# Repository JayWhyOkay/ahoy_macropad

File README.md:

# Ahoy -- XT Macropad

Ahoy is a simple but functional macropad designed for people who need both a numpad and a macro column for work/productivity. The features include:

- Numpad with split mod support
- 10 additional keys for macros
- Rotary encoder support on top left key
- 8 addressable RGB LEDs 
- Num, Caps, Scroll Lock Indicator LEDs
- USB C (USB 2.0)

The layout for the macropad can be seen below: 

## Instructions
To replicate the PCB and the case, the guide can be found below: 
- [Instructions on ordering this PCB](ahoy_pcb/gerber/production/)
- [Instructions on ordering the case](acrylic_case/)

## Project Status
- [x] Design PCB
- [x] Design Case
- [x] Order Prototypes
- [x] Create bootloader
- [x] Create QMK/VIA firmware
- [x] Revise prototypes
### Todo List
- [x] Revise LED cutouts on acrylic case 
- [ ] \(Optional) add art/silkscreen
- [ ] Clear @todo 's
- [ ] Update to modern QMK standards!
## Licensing 
The following project was built on Gondolindrim's [Acheron Project](https://github.com/AcheronProject) and ai03's [PCB guide](https://wiki.ai03.com/books/pcb-design/chapter/pcb-designer-guide) and [design files](https://github.com/ai03-2725). As such, the licensing will follow their licensing arrangement on top of this project's licensing, which can be found [here](LICENSE).

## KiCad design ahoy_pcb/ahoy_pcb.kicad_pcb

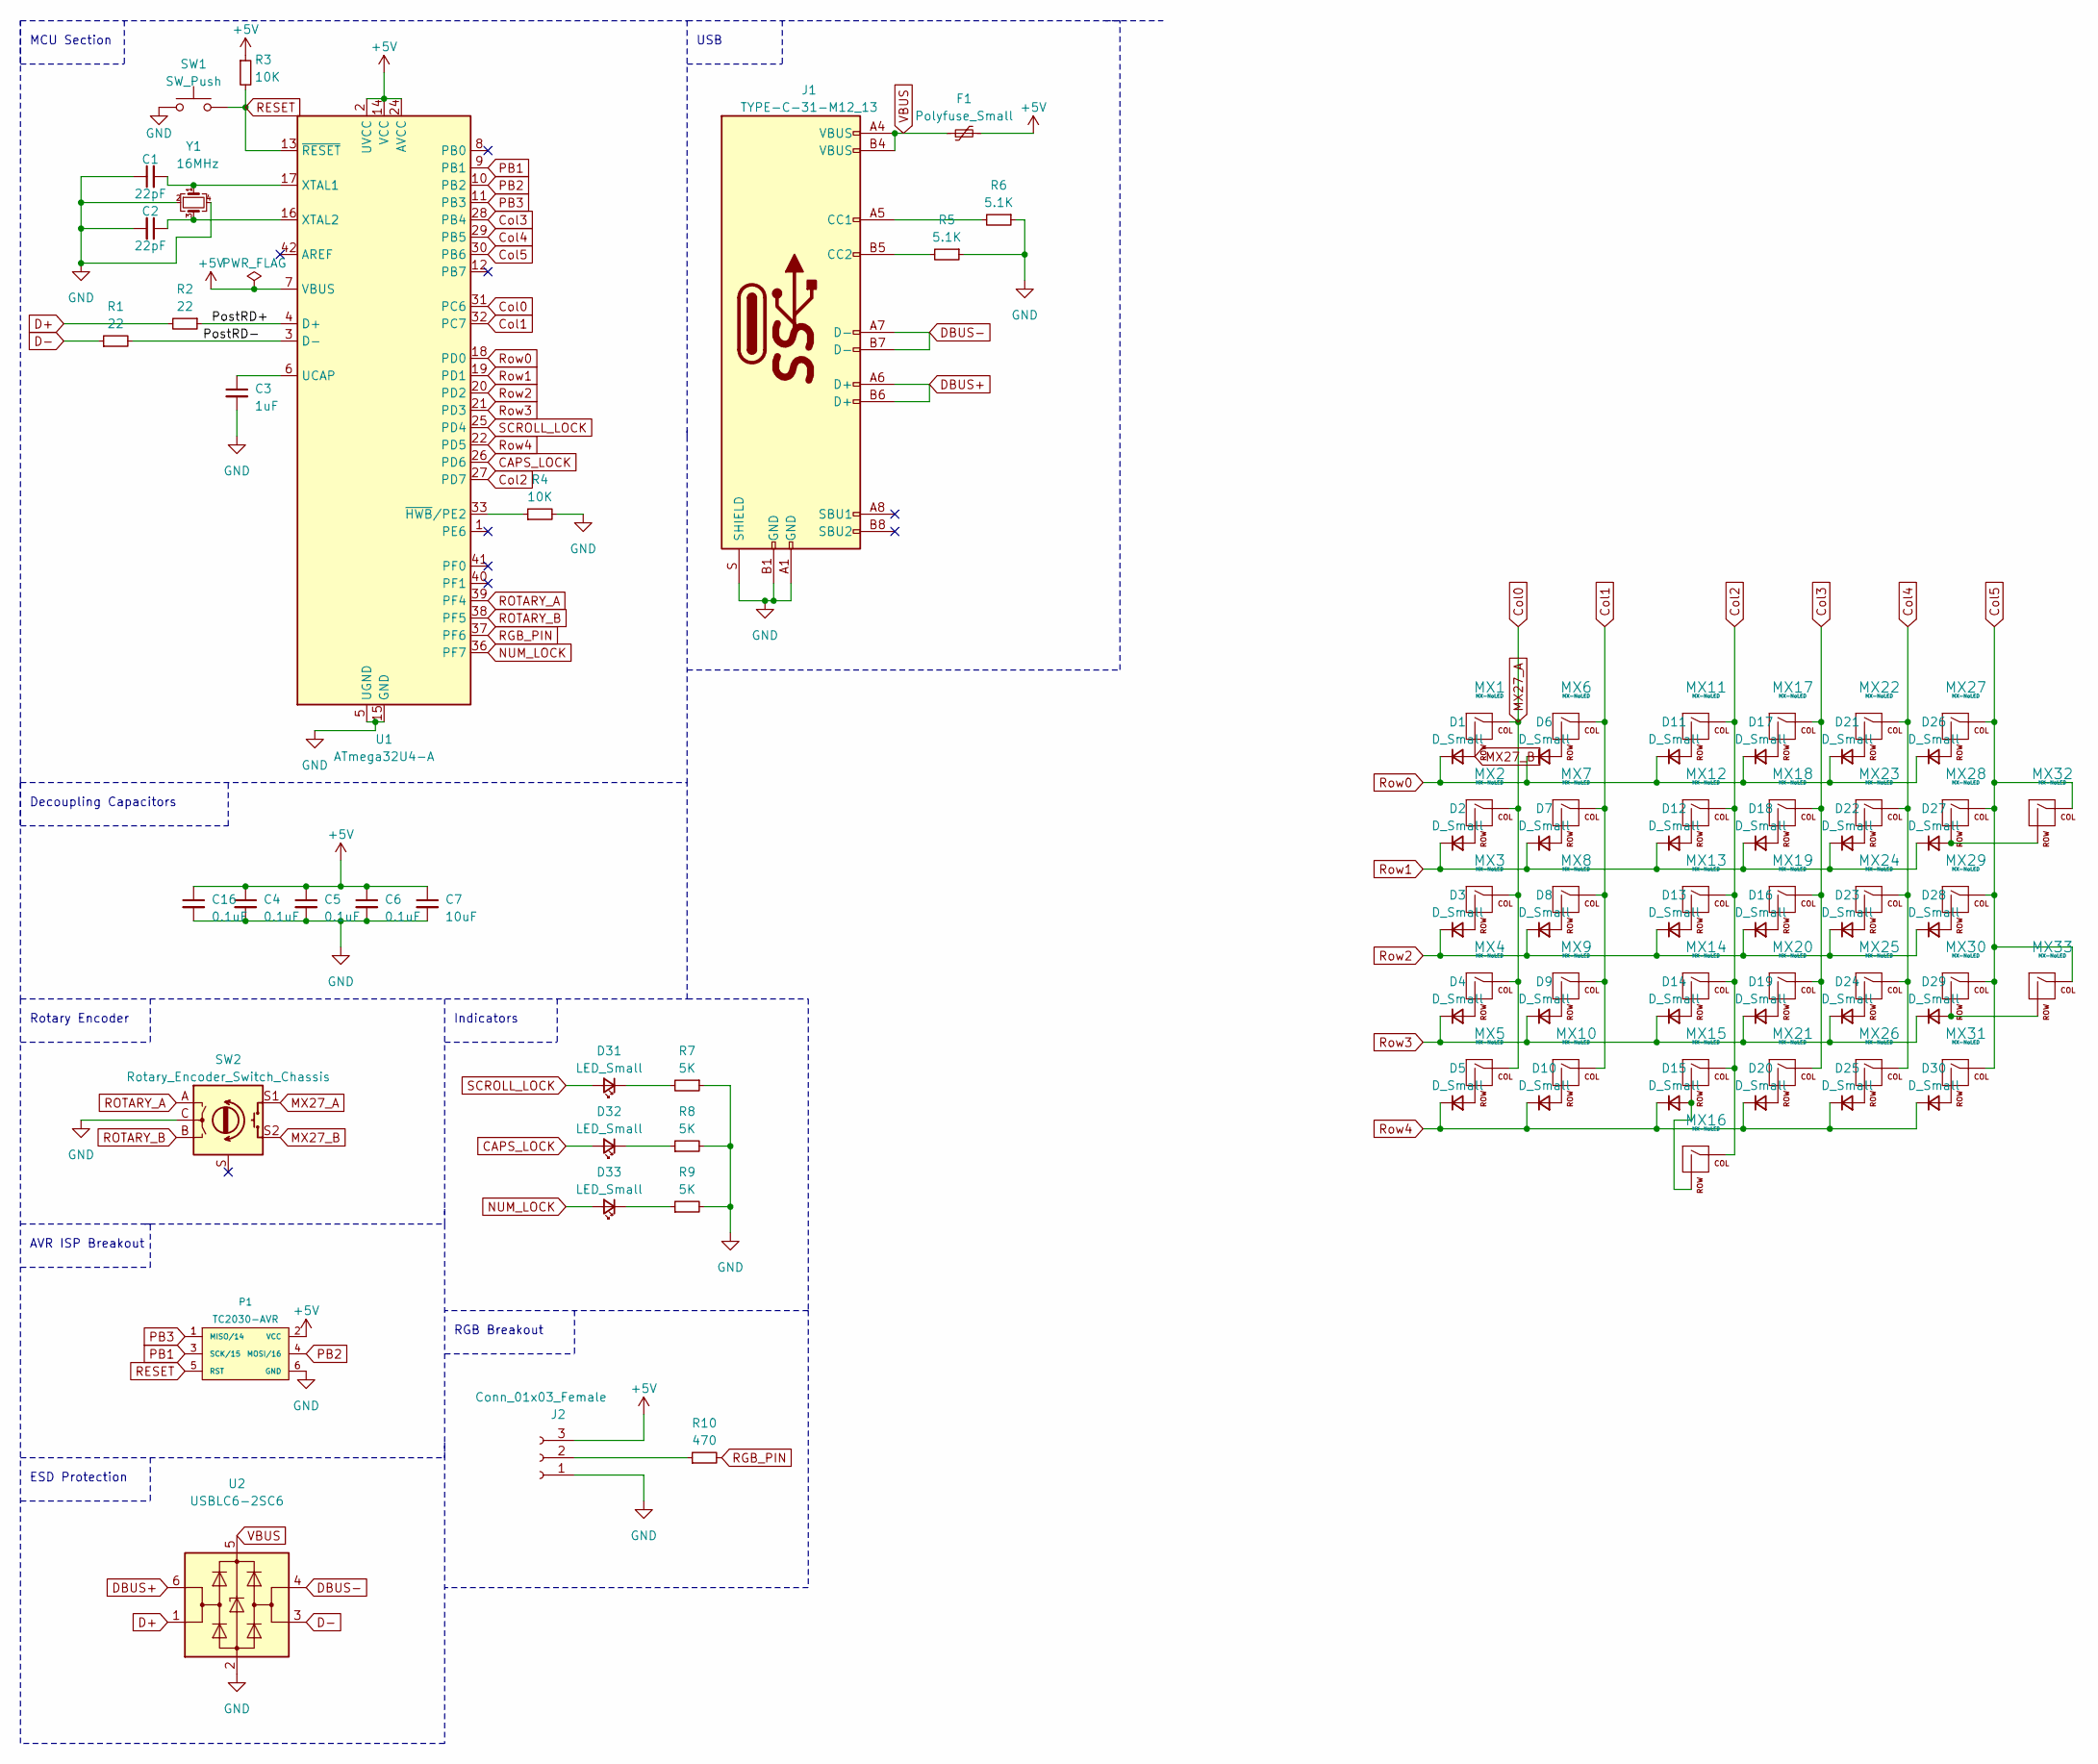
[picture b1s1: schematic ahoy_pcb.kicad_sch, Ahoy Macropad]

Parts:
C1, C2: 22pF; C_0805_2012Metric
C3: 1uF; C_0805_2012Metric
C4, C5, C6, C16: 0.1uF; C_0805_2012Metric
C7: 10uF; C_0805_2012Metric
D1, D2, D3, D4, D5, D6, D7, D8, D9, D10, D11, D12, D13, D14, D15, D16, D17, D18, D19, D20, D21, D22, D23, D24, D25, D26, D27, D28, D29, D30: D_Small; D_SOD-123
D31, D32, D33: LED_Small; LED_D3.0mm-Pretty
F1: Polyfuse_Small; Fuse_1206_3216Metric
J1: TYPE-C-31-M12_13; TYPE-C-31-M-12
J2: Conn_01x03_Female; PinHeader_1x3_staggered_P2.54mm_Vertical
MX1, MX2, MX3, MX4, MX5, MX6, MX7, MX8, MX9, MX10, MX11, MX12, MX13, MX14, MX15, MX17, MX18, MX19, MX20, MX21, MX22, MX23, MX24, MX25, MX26, MX27, MX28, MX29, MX30, MX31: MX-NoLED; MXOnly-1U-NoLED
MX16, MX32, MX33: MX-NoLED; MXOnly-2U-ReversedStabilizers-NoLED
P1: TC2030-AVR; PinHeader_2x3_P2.54mm_Vertical
R1, R2: 22; R_0805_2012Metric
R3, R4: 10K; R_0805_2012Metric
R5, R6: 5.1K; R_0805_2012Metric
R7, R8, R9: 5K; R_0805_2012Metric
R10: 470; R_0805_2012Metric
SW1: SW_Push; SW_TS-1187A-B-A-B
SW2: Rotary_Encoder_Switch_Chassis; RotaryEncoder_Alps_EC11E-Switch_Vertical_H20mm_CircularMoun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
U1: ATmega32U4-A; TQFP-44_10x10mm_P0.8mm
U2: USBLC6-2SC6; SOT-23-6
Y1: 16MHz; Crystal_SMD_3225-4Pin_3.2x2.5mm

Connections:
+5V: C4.1, C5.1, C6.1, C7.1, C16.1, F1.2, J2.3, P1.2 (VCC), R3.1, U1.2 (UVCC), U1.7 (VBUS), U1.14 (VCC), U1.24 (AVCC), U1.34 (VCC), U1.44 (AVCC)
/PostRD+: R2.1, U1.4 (D+)
/PostRD-: R1.2, U1.3 (D-)
CAPS_LOCK: D32.2 (A), U1.26 (PD6)
Col0: MX1.1 (COL), MX2.1 (COL), MX3.1 (COL), MX4.1 (COL), MX5.1 (COL), SW2.S1, U1.31 (PC6)
Col1: MX6.1 (COL), MX7.1 (COL), MX8.1 (COL), MX9.1 (COL), MX10.1 (COL), U1.32 (PC7)
Col2: MX11.1 (COL), MX12.1 (COL), MX13.1 (COL), MX14.1 (COL), MX15.1 (COL), MX16.1 (COL), U1.27 (PD7)
Col3: MX17.1 (COL), MX18.1 (COL), MX19.1 (COL), MX20.1 (COL), MX21.1 (COL), U1.28 (PB4)
Col4: MX22.1 (COL), MX23.1 (COL), MX24.1 (COL), MX25.1 (COL), MX26.1 (COL), U1.29 (PB5)
Col5: MX27.1 (COL), MX28.1 (COL), MX29.1 (COL), MX30.1 (COL), MX31.1 (COL), MX32.1 (COL), MX33.1 (COL), U1.30 (PB6)
D+: R2.2, U2.1 (I/O1)
D-: R1.1, U2.3 (I/O2)
DBUS+: J1.A6 (D+), J1.B6 (D+), U2.6 (I/O1)
DBUS-: J1.A7 (D-), J1.B7 (D-), U2.4 (I/O2)
GND: C1.1, C2.2, C3.2, C4.2, C5.2, C6.2, C7.2, C16.2, J1.A1 (GND), J1.B1 (GND), J1.S (SHIELD), J2.1, P1.6 (GND), R4.2, R5.1, R6.1, R7.1, R8.2, R9.2, SW1.1, SW2.C, U1.5 (UGND), U1.15 (GND), U1.23 (GND), U1.35 (GND), U1.43 (GND), U2.2 (GND), Y1.2, Y1.4
MX27_B: D1.2 (A), MX1.2 (ROW), SW2.S2
NUM_LOCK: D33.2 (A), U1.36 (PF7)
unnamed: C1.2, U1.17 (XTAL1), Y1.1
unnamed: C2.1, U1.16 (XTAL2), Y1.3
unnamed: C3.1, U1.6 (UCAP)
unnamed: D2.2 (A), MX2.2 (ROW)
unnamed: D3.2 (A), MX3.2 (ROW)
unnamed: D4.2 (A), MX4.2 (ROW)
unnamed: D5.2 (A), MX5.2 (ROW)
unnamed: D6.2 (A), MX6.2 (ROW)
unnamed: D7.2 (A), MX7.2 (ROW)
unnamed: D8.2 (A), MX8.2 (ROW)
unnamed: D9.2 (A), MX9.2 (ROW)
unnamed: D10.2 (A), MX10.2 (ROW)
unnamed: D11.2 (A), MX11.2 (ROW)
unnamed: D12.2 (A), MX12.2 (ROW)
unnamed: D13.2 (A), MX13.2 (ROW)
unnamed: D14.2 (A), MX14.2 (ROW)
unnamed: D15.2 (A), MX15.2 (ROW), MX16.2 (ROW)
unnamed: D16.2 (A), MX19.2 (ROW)
unnamed: D17.2 (A), MX17.2 (ROW)
unnamed: D18.2 (A), MX18.2 (ROW)
unnamed: D19.2 (A), MX20.2 (ROW)
unnamed: D20.2 (A), MX21.2 (ROW)
unnamed: D21.2 (A), MX22.2 (ROW)
unnamed: D22.2 (A), MX23.2 (ROW)
unnamed: D23.2 (A), MX24.2 (ROW)
unnamed: D24.2 (A), MX25.2 (ROW)
unnamed: D25.2 (A), MX26.2 (ROW)
unnamed: D26.2 (A), MX27.2 (ROW)
unnamed: D27.2 (A), MX28.2 (ROW), MX32.2 (ROW)
unnamed: D28.2 (A), MX29.2 (ROW)
unnamed: D29.2 (A), MX30.2 (ROW), MX33.2 (ROW)
unnamed: D30.2 (A), MX31.2 (ROW)
unnamed: D31.1 (K), R7.2
unnamed: D32.1 (K), R8.1
unnamed: D33.1 (K), R9.1
unnamed: J1.A5 (CC1), R6.2
unnamed: J1.B5 (CC2), R5.2
unnamed: R4.1, U1.33 (~HWB~/PE2)
unnamed: J2.2, R10.1
PB1: P1.3 (SCK/15), U1.9 (PB1)
PB2: P1.4 (MOSI/16), U1.10 (PB2)
PB3: P1.1 (MISO/14), U1.11 (PB3)
RESET: P1.5 (RST), R3.2, SW1.2, U1.13 (~RESET)
RGB_PIN: R10.2, U1.37 (PF6)
ROTARY_A: SW2.A, U1.39 (PF4)
ROTARY_B: SW2.B, U1.38 (PF5)
Row0: D1.1 (K), D6.1 (K), D11.1 (K), D17.1 (K), D21.1 (K), D26.1 (K), U1.18 (PD0)
Row1: D2.1 (K), D7.1 (K), D12.1 (K), D18.1 (K), D22.1 (K), D27.1 (K), U1.19 (PD1)
Row2: D3.1 (K), D8.1 (K), D13.1 (K), D16.1 (K), D23.1 (K), D28.1 (K), U1.20 (PD2)
Row3: D4.1 (K), D9.1 (K), D14.1 (K), D19.1 (K), D24.1 (K), D29.1 (K), U1.21 (PD3)
Row4: D5.1 (K), D10.1 (K), D15.1 (K), D20.1 (K), D25.1 (K), D30.1 (K), U1.22 (PD5)
SCROLL_LOCK: D31.2 (A), U1.25 (PD4)
VBUS: F1.1, J1.A4 (VBUS), J1.B4 (VBUS), U2.5 (VBUS)

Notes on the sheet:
MCU Section
Decoupling Capacitors
Rotary Encoder
AVR ISP Breakout
ESD Protection
Indicators
RGB Breakout
USB

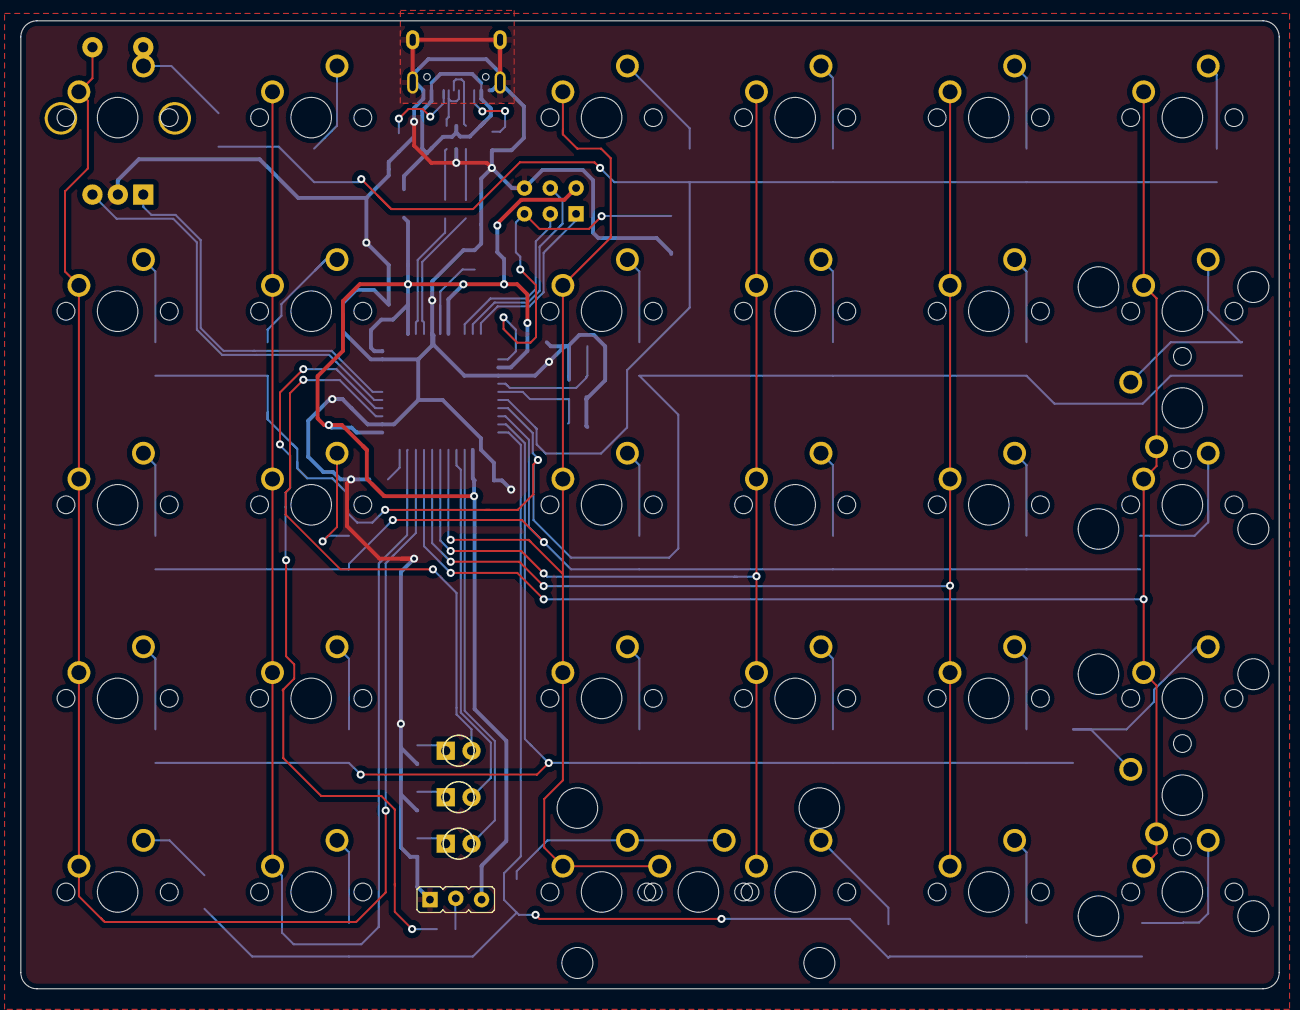
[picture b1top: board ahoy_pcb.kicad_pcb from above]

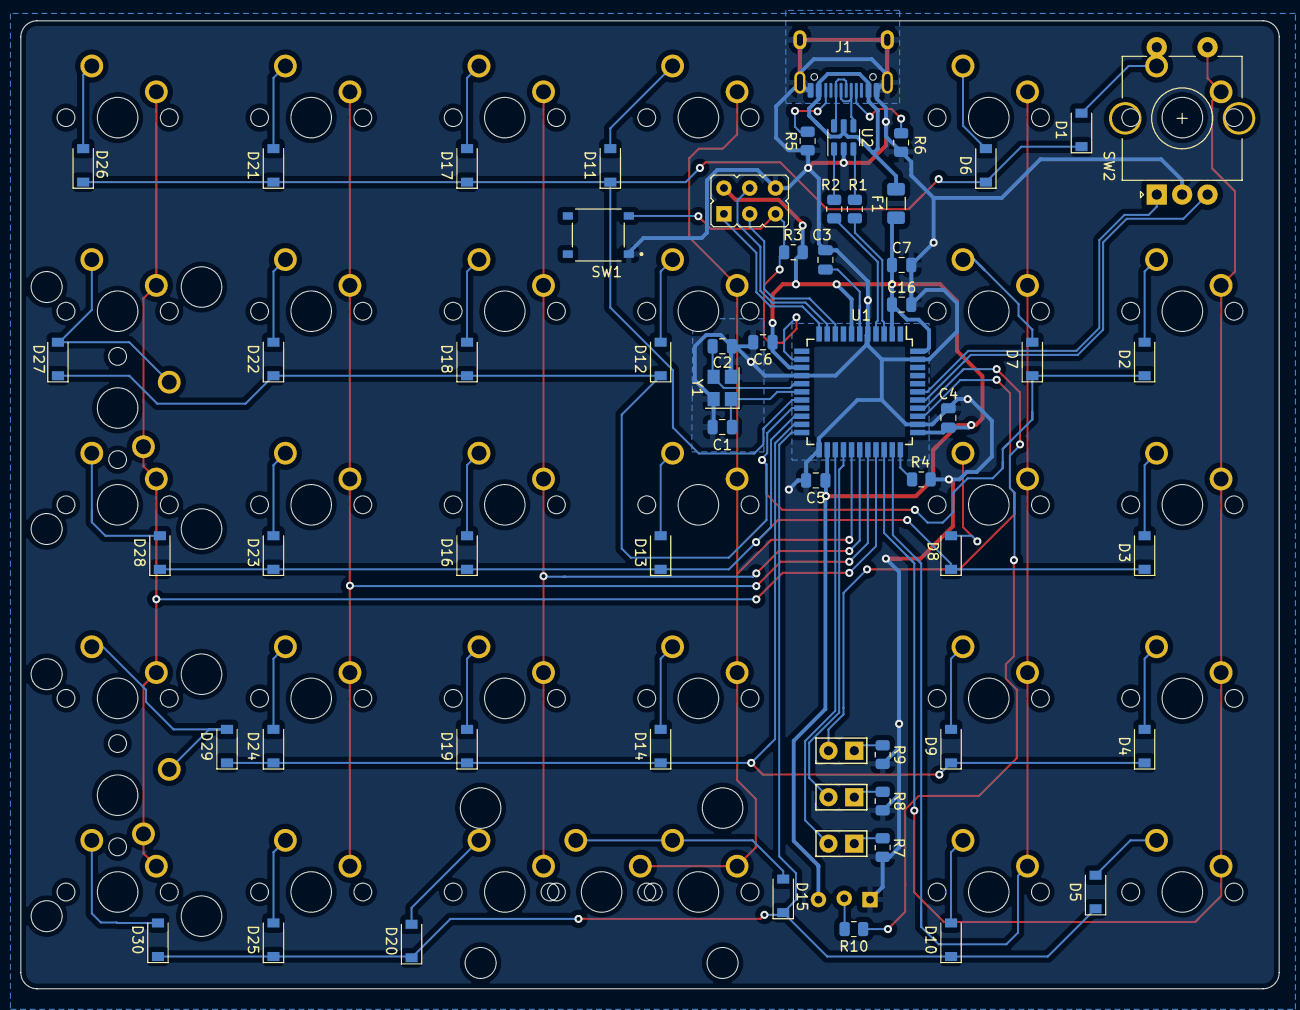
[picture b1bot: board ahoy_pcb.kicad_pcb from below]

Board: 2 copper layers, 123.8 x 95.2 mm, 93 parts (56 on the bottom side), 70 nets.

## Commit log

2021-07-18 Rev 1 Update
2021-07-18 some refactoring
2021-07-18 update readme pt 1
2021-07-18 Updated READMEs pt 2
2021-10-02 More updates
2021-12-12 Upload of final project
2023-02-22 Final-Ish Commit
